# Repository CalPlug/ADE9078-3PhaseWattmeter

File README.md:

# ADE9078-3PhaseWattmeter
An Isolated design demo board using the ADE7953 3 phase AC wattmeter.  Design allows both WYE (STAR) and Delta (TRIANGLE) distributions to be measured along with Blondel and non-Blondel measurement schemes.  Project includes a demo ADE9078 Arduino firmware

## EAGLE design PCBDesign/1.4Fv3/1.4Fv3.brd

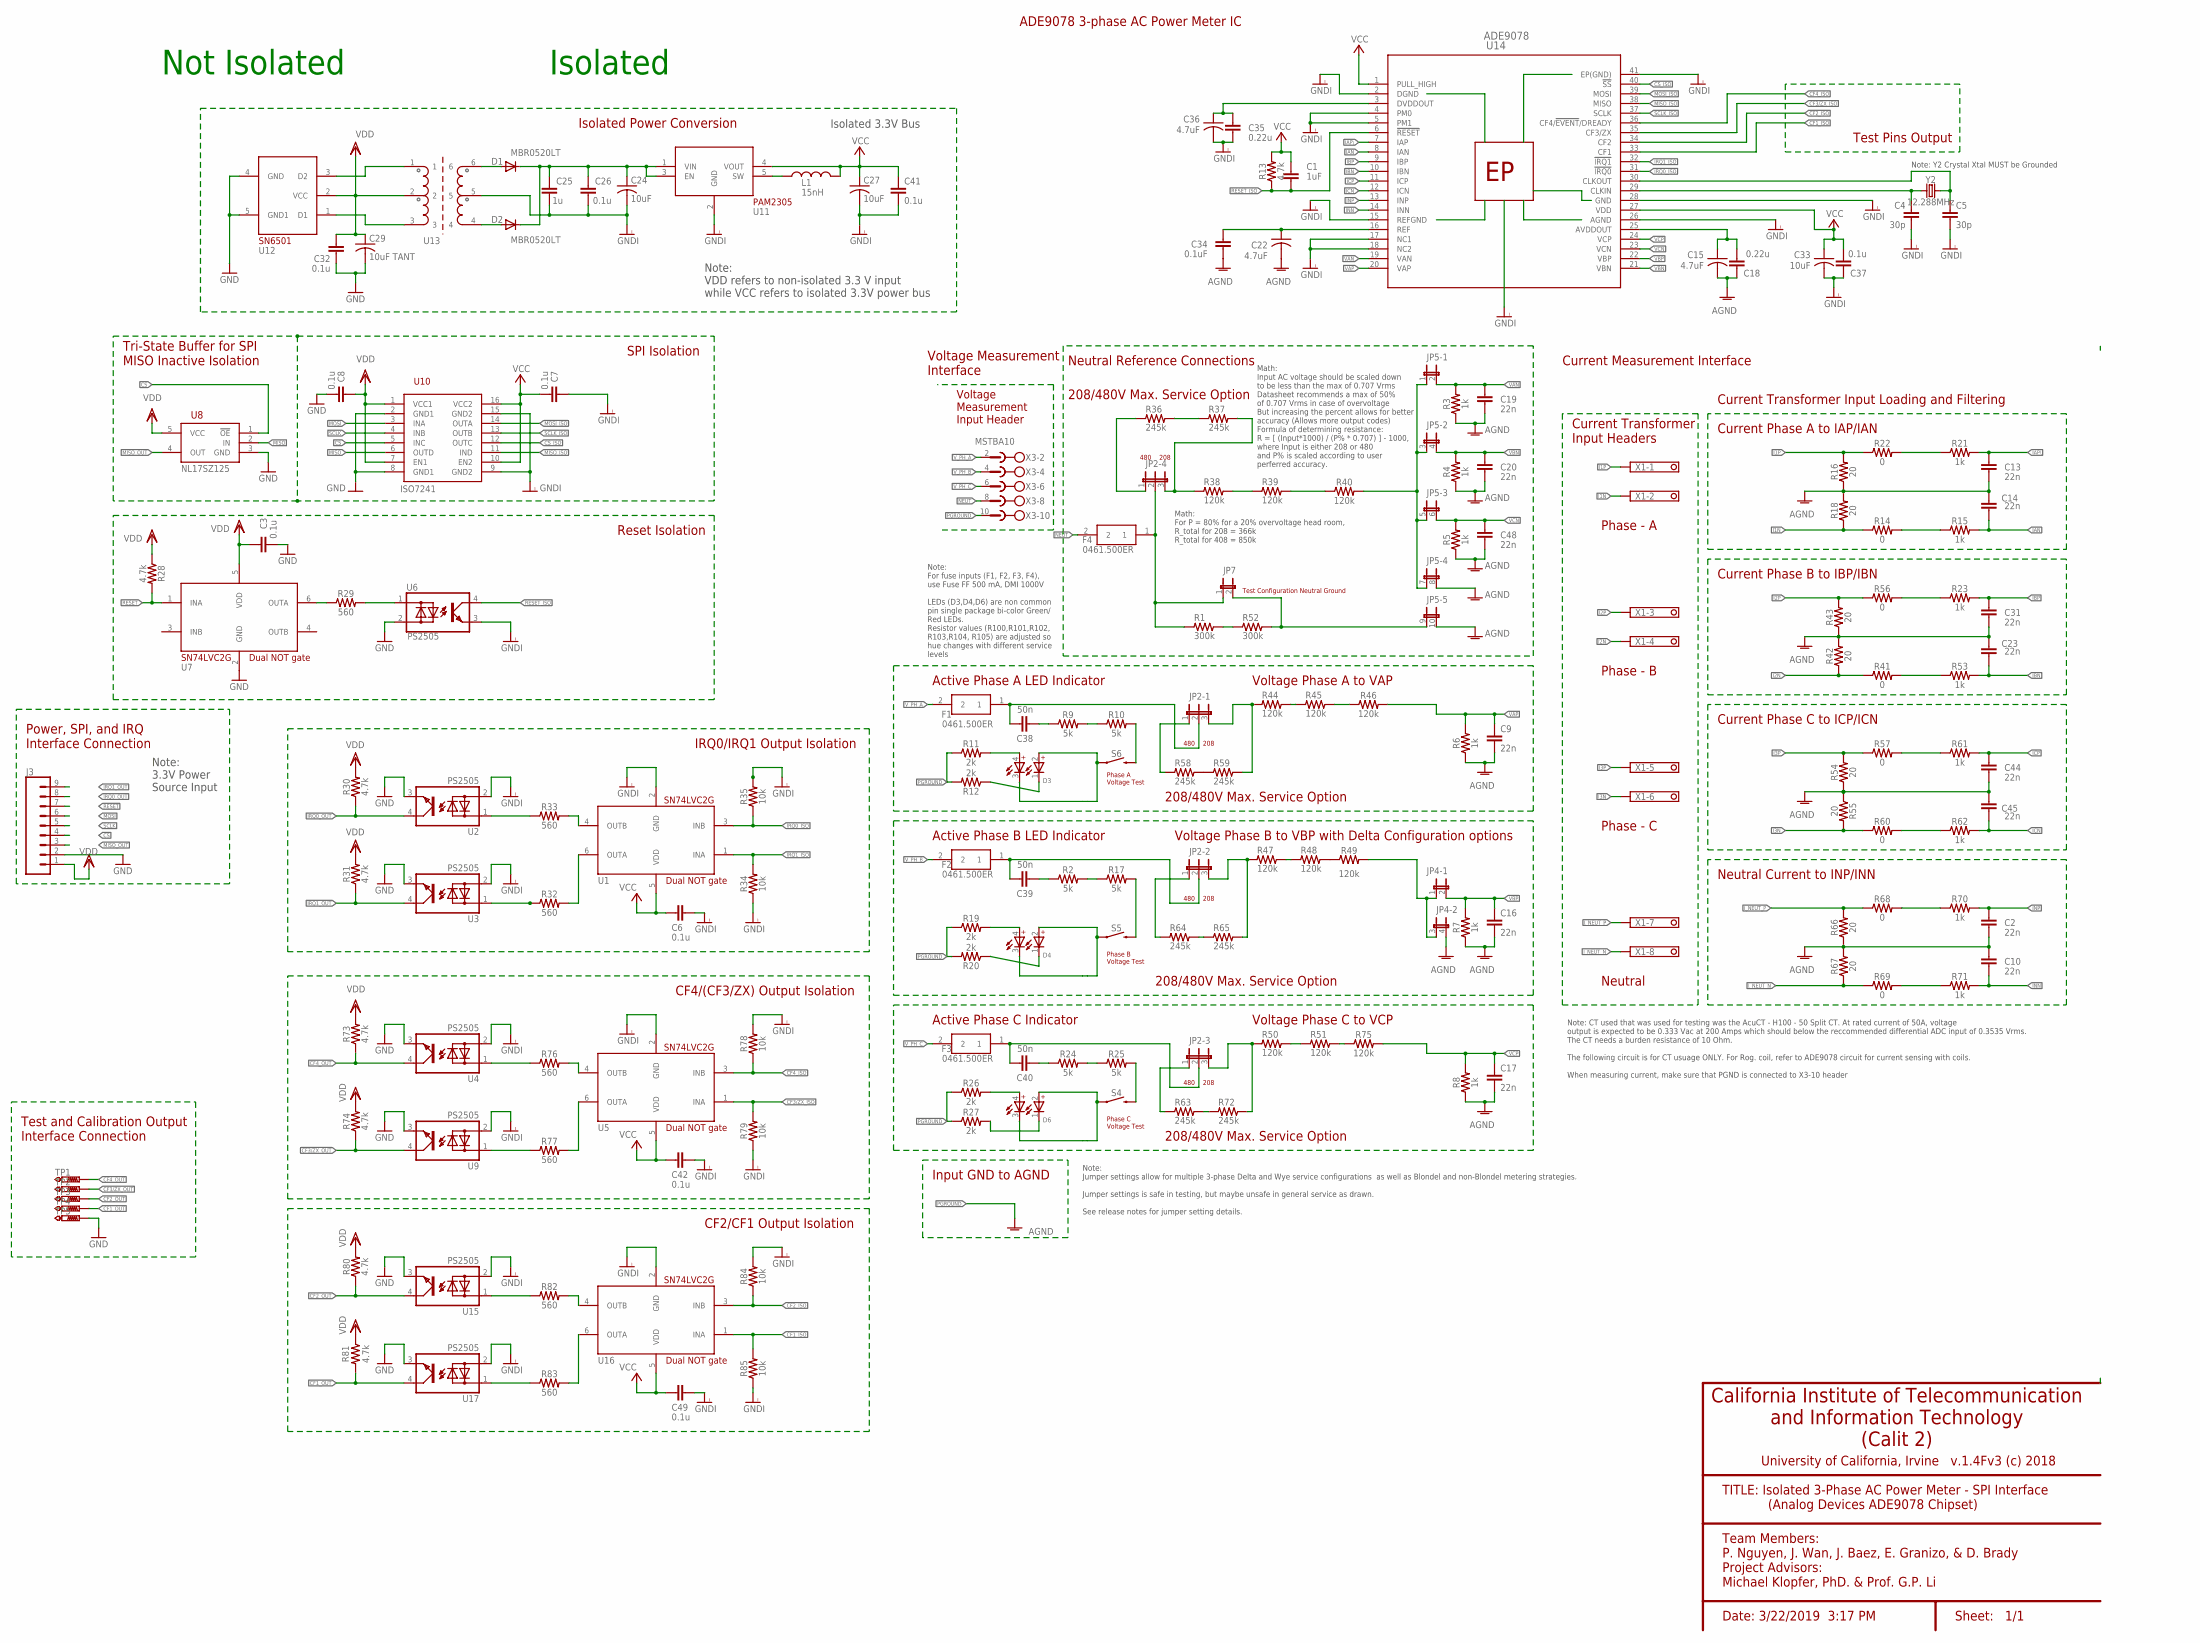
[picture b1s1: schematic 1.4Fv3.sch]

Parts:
C1: 1uF; 0603; MPN MC0805B104K500A5.08MM
C2, C9, C10, C13, C14, C16, C17, C19, C20, C23, C31, C44, C45, C48: 22n; 0402-CAP; MPN C0603C223K5RACTU
C3, C6, C7, C8, C26, C32, C37, C41, C42, C49: 0.1u; 0402-CAP; MPN C0603X5R1A104K030BC
C4, C5: 30p; 0402-CAP; MPN MC0402N180J500CT
C15, C22, C36: 4.7uF; C0603; MPN C1608X5R1A106K080AC
C18, C35: 0.22u; 0402-CAP; MPN MC0805F224Z500CT
C24, C27, C33: 10uF; C0603; MPN C1608X5R1A106K080AC
C25: 1u; 0402-CAP; MPN C0603X5R1A104K030BC
C29: 10uF TANT; C0603; MPN 195D106X96R3V2T
C34: 0.1uF; 0402-CAP; MPN C0603X5R1A104K030BC
C38, C39, C40: 50n; 0402-CAP; MPN C0603C223K5RACTU
D1, D2: MBR0520LT; SOD123; MPN MBR0520LT1G.
D3, D4, D6: WL-SBCW_0606_150066SV74000; WL-SBCW_0606
F1, F2, F3, F4: 0461.500ER; FUSC10131X312N
J3: CONN_09; 1X09; MPN 350547-1
JP2-1, JP2-2, JP2-3, JP2-4: JP2E; JP2
JP4: JP2QE; JP2Q; MPN 350547-1
JP5: JP5QE; JP5Q; MPN 350547-1
JP7: JP1E; JP1
L1: 15nH; 0402-RES
R1, R52: 300k; R2010
R2, R9, R10, R17, R24, R25: 5k; 0603
R3, R4, R5, R6, R7, R8, R15, R21, R23, R53, R61, R62, R70, R71: 1k; 0603
R11, R12, R19, R20, R26, R27: 2k; 0603
R13, R28, R30, R31, R73, R74, R80, R81: 4.7k; 0603
R14, R22, R41, R56, R57, R60, R68, R69: 0; 0603
R16, R18, R42, R43, R54, R55, R66, R67: 20; 0603
R29, R32, R33, R76, R77, R82, R83: 560; 0603
R34, R35, R78, R79, R84, R85: 10k; 0603
R36, R37, R58, R59, R63, R64, R65, R72: 245k; R2010
R38, R39, R44, R45, R47, R48, R50, R51: 120k; R2010
R40, R46, R49, R75: 120k; 0603
S4, S5, S6: MOMENTARY-SWITCH-SPST-SMD-4.5MM; TACTILE_SWITCH_SMD_4.5MM
TP1, TP2, TP3, TP4, TP5: PTR1B1,27; B1,27
U1, U5, U7, U16: SN74LVC; DCKT; MPN SN74LVC1G34DBVR
U2, U3, U4, U6, U9, U15, U17: PS2505; MPN PS2505-4-A
U8: NL17SZ125; MPN SN74LVC1G125DRLR
U10: ISO7241; 16-SOIC; MPN ISO7241CQDWRQ1
U11: PAM2305; TSOT25
U12: SN6501; SOT-23-5; MPN SN6501DBVT
U13: TRANSFO_3.3
U14: ADE9078; CP_40_7; MPN ADE9078ACPZ
X1: 1751303
X3: MSTBA10
Y2: 12.288MHz; CRYSTAL-SMD-5X3.2-4PAD

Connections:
AGND: C2.1, C9.2, C10.2, C13.1, C14.2, C15.2, C16.2, C17.2, C18.1, C19.2, C20.2, C22.2, C23.2, C31.1, C34.1, C44.1, C45.2, C48.2, JP4.4 (2), JP5.8 (2), JP5.10 (2), R3.1, R4.1, R5.1, R6.1, R7.1, R8.1, R16.1, R18.2, R42.2, R43.1, R54.1, R55.1, R66.1, R67.2
AVDDOUT: C15.1, C18.2, U14.25 (AVDDOUT)
CF1_ISO: R85.2, U14.33 (CF1), U16.1 (INA)
CF1_OUT: R81.2, TP4.TP, U17.4 (COLLERTOR)
CF2_ISO: R84.1, U14.34 (CF2), U16.3 (INB)
CF2_OUT: R80.1, TP3.TP, U15.4 (COLLERTOR)
CF3/ZX_ISO: R79.2, U5.1 (INA), U14.35 (CF3/ZX)
CF3/ZX_OUT: R74.1, TP2.TP, U9.4 (COLLERTOR)
CF4_ISO: R78.1, U5.3 (INB), U14.36 (CF4/!EVENT!/DREADY)
CF4_OUT: R73.1, TP1.TP, U4.4 (COLLERTOR)
CS: J3.4, U8.1 (!OE), U10.5 (INC)
CS_ISO: U10.12 (OUTC), U14.40 (!SS)
DVDDOUT: C35.2, C36.1, U14.3 (DVDDOUT)
GND: C3.2, C8.2, C29.2, C32.1, J3.2, TP5.TP, U2.3 (EMITTER), U3.3 (EMITTER), U4.3 (EMITTER), U6.2 (CATHODE), U7.2 (GND), U8.3 (GND), U9.3 (EMITTER), U10.2 (GND1), U10.8 (GND1), U12.4 (GND), U12.5 (GND1), U15.3 (EMITTER), U17.3 (EMITTER)
GNDI: C4.1, C5.2, C6.1, C7.1, C24.2, C25.1, C26.1, C27.2, C33.2, C35.1, C36.2, C37.1, C41.2, C42.1, C49.1, R34.1, R35.2, R78.2, R79.1, R84.2, R85.1, U1.2 (GND), U2.2 (CATHODE), U3.2 (CATHODE), U4.2 (CATHODE), U5.2 (GND), U6.3 (EMITTER), U9.2 (CATHODE), U10.9 (GND2), U10.15 (GND2), U11.2 (GND), U13.5, U14.2 (DGND), U14.4 (PM0), U14.5 (PM1), U14.15 (REFGND), U14.17 (NC1), U14.18 (NC2), U14.26 (AGND), U14.28 (GND), U14.41 (EP(GND)), U15.2 (CATHODE), U16.2 (GND), U17.2 (CATHODE)
I1N: R14.1, R18.1, X1.2
I1P: R16.2, R22.1, X1.1
I2N: R41.1, R42.1, X1.4
I2P: R43.2, R56.1, X1.3
I3N: R55.2, R60.1, X1.6
I3P: R54.2, R57.1, X1.5
IAN: C14.1, R15.2, U14.8 (IAN)
IAP\: C13.2, R21.2, U14.7 (IAP)
IBN: C23.1, R53.2, U14.10 (IBN)
IBP: C31.2, R23.2, U14.9 (IBP)
ICN: C45.1, R62.2, U14.12 (ICN)
ICP: C44.2, R61.2, U14.11 (ICP)
INN: C10.1, R71.2, U14.14 (INN)
INP: C2.2, R70.2, U14.13 (INP)
IRQ0_ISO: R35.1, U1.3 (INB), U14.31 (!IRQ0)
IRQ0_OUT: J3.8, R30.1, U2.4 (COLLERTOR)
IRQ1_ISO: R34.2, U1.1 (INA), U14.32 (!IRQ1)
IRQ1_OUT: J3.9, R31.1, U3.4 (COLLERTOR)
I_NEUT_N: R67.1, R69.1, X1.8
I_NEUT_P: R66.2, R68.1, X1.7
MISO: U8.2 (IN), U10.6 (OUTD)
MISO_ISO: U10.11 (IND), U14.38 (MISO)
MISO_OUT: J3.3, U8.4 (OUT)
MOSI: J3.6, U10.3 (INA)
MOSI_ISO: U10.14 (OUTA), U14.39 (MOSI)
unnamed: C5.1, U14.30 (CLKOUT), Y2.3 (2)
unnamed: R21.1, R22.2
unnamed: R14.2, R15.1
unnamed: L1.1, U11.5 (SW)
unnamed: R57.2, R61.1
unnamed: R60.2, R62.1
unnamed: C38.2, R9.1
unnamed: R32.2, U1.6 (OUTA)
unnamed: R32.1, U3.1 (ANODE)
unnamed: C4.2, U14.29 (CLKIN), Y2.1
unnamed: R25.2, S4.1 (2), S4.4 (2)
unnamed: D1.A, U13.6
unnamed: C24.1, C25.2, C26.2, D1.C, D2.C, U11.1 (VIN), U11.3 (EN)
unnamed: D2.A, U13.4
unnamed: U12.3 (D2), U13.1
unnamed: U12.1 (D1), U13.3
unnamed: R23.1, R56.2
unnamed: R29.2, U6.1 (ANODE)
unnamed: R29.1, U7.6 (OUTA)
unnamed: R41.2, R53.1
unnamed: R9.2, R10.1
unnamed: R33.2, U1.4 (OUTB)
unnamed: R76.2, U5.4 (OUTB)
unnamed: R1.2, R52.1
unnamed: R64.2, R65.1
unnamed: R33.1, U2.1 (ANODE)
unnamed: JP2-1.1, R58.1
unnamed: R58.2, R59.1
unnamed: R10.2, S6.1 (2), S6.4 (2)
unnamed: JP2-1.3, R44.1, R59.2
unnamed: JP2-2.1, R64.1
unnamed: JP2-2.3, R47.1, R65.2
unnamed: R63.2, R72.1
unnamed: R68.2, R70.1
unnamed: JP2-4.3, R37.2, R38.1
unnamed: JP2-4.1, R36.1
unnamed: R36.2, R37.1
unnamed: JP5.9 (1), JP7.2, R52.2
unnamed: R69.2, R71.1
unnamed: C39.2, R2.1
unnamed: R2.2, R17.1
unnamed: R17.2, S5.1 (2), S5.4 (2)
unnamed: D3.1 (C2), R12.1
unnamed: D6.2 (A2), D6.3 (C1), S4.2 (1), S4.3 (1)
unnamed: C40.2, R24.1
unnamed: R24.2, R25.1
unnamed: D3.4 (A1), R11.2
unnamed: D4.2 (A2), D4.3 (C1), S5.2 (1), S5.3 (1)
unnamed: R76.1, U4.1 (ANODE)
unnamed: R77.1, U9.1 (ANODE)
unnamed: R77.2, U5.6 (OUTA)
unnamed: JP5.1, JP5.3 (1), JP5.5 (1), JP5.7 (1), R40.2
unnamed: R82.1, U15.1 (ANODE)
unnamed: R83.1, U17.1 (ANODE)
unnamed: R83.2, U16.6 (OUTA)
unnamed: D3.2 (A2), D3.3 (C1), S6.2 (1), S6.3 (1)
unnamed: D4.4 (A1), R19.2
unnamed: R45.2, R46.1
unnamed: C40.1, F3.1, JP2-3.2
unnamed: F4.1, JP2-4.2, JP7.1, R1.1
unnamed: C38.1, F1.1, JP2-1.2
unnamed: R48.2, R49.1
unnamed: JP2-3.3, R50.1, R72.2
unnamed: JP4.1, JP4.3 (1), R49.2
unnamed: C39.1, F2.1, JP2-2.2
unnamed: JP2-3.1, R63.1
unnamed: R50.2, R51.1
unnamed: R51.2, R75.1
unnamed: R82.2, U16.4 (OUTB)
unnamed: R44.2, R45.1
unnamed: R47.2, R48.1
unnamed: R38.2, R39.1
unnamed: R39.2, R40.1
unnamed: D4.1 (C2), R20.1
unnamed: D6.1 (C2), R27.2
unnamed: D6.4 (A1), R26.2
NEUT: F4.2, X3.8
PGROUND: R11.1, R12.2, R19.1, R20.2, R26.1, R27.1, X3.10
REF: C22.1, C34.2, U14.16 (REF)
RESET: J3.7, R28.2, U7.1 (INA)
RESET_ISO: C1.2, R13.1, U6.4 (COLLERTOR), U14.6 (!RESET)
SCLK: J3.5, U10.4 (INB)
SCLK_ISO: U10.13 (OUTB), U14.37 (SCLK)
VAN: C19.1, JP5.2, R3.2, U14.19 (VAN)
VAP: C9.1, R6.2, R46.2, U14.20 (VAP)
VBN: C20.1, JP5.4 (2), R4.2, U14.21 (VBN)
VBP: C16.1, JP4.2, R7.2, U14.22 (VBP)
VCC: C1.1, C6.2, C7.2, C27.1, C33.1, C37.2, C41.1, C42.2, C49.2, L1.2, R13.2, U1.5 (VDD), U5.5 (VDD), U10.10 (EN2), U10.16 (VCC2), U11.4 (VOUT), U14.1 (PULL_HIGH), U14.27 (VDD), U16.5 (VDD)
VCN: C48.1, JP5.6 (2), R5.2, U14.23 (VCN)
VCP: C17.1, R8.2, R75.2, U14.24 (VCP)
VDD: C3.1, C8.1, C29.1, C32.2, J3.1, R28.1, R30.2, R31.2, R73.2, R74.2, R80.2, R81.1, U7.5 (VDD), U8.5 (VCC), U10.1 (VCC1), U10.7 (EN1), U12.2 (VCC), U13.2
V_PH_A: F1.2, X3.2
V_PH_B: F2.2, X3.4
V_PH_C: F3.2, X3.6

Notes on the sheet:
Not Isolated
Isolated
Isolated Power Conversion
Note: VDD refers to non-isolated 3.3 V input while VCC refers to isolated 3.3V power bus
Isolated 3.3V Bus
ISO7241
SPI Isolation
Tri-State Buffer for SPI MISO Inactive Isolation
Dual NOT gate
Reset Isolation
Power, SPI, and IRQ Interface Connection
Note: 3.3V Power Source Input
IRQ0/IRQ1 Output Isolation
CF4/(CF3/ZX) Output Isolation
Test and Calibration Output Interface Connection
CF2/CF1 Output Isolation
ADE9078 3-phase AC Power Meter IC
Current Measurement Interface
Test Pins Output
Voltage Measurement Interface
Voltage Measurement Input Header
Voltage Phase A to VAP
Voltage Phase B to VBP with Delta Configuration options
Voltage Phase C to VCP
Input GND to AGND
Neutral Reference Connections
Current Transformer Input Headers
Current Phase A to IAP/IAN
Current Phase B to IBP/IBN
Current Phase C to ICP/ICN
Neutral Current to INP/INN
Active Phase A LED Indicator
Active Phase B LED Indicator
Active Phase C Indicator
Current Transformer Input Loading and Filtering
Phase - A
Phase - B
Phase - C
Neutral
Date: 3/22/2019 3:17 PM

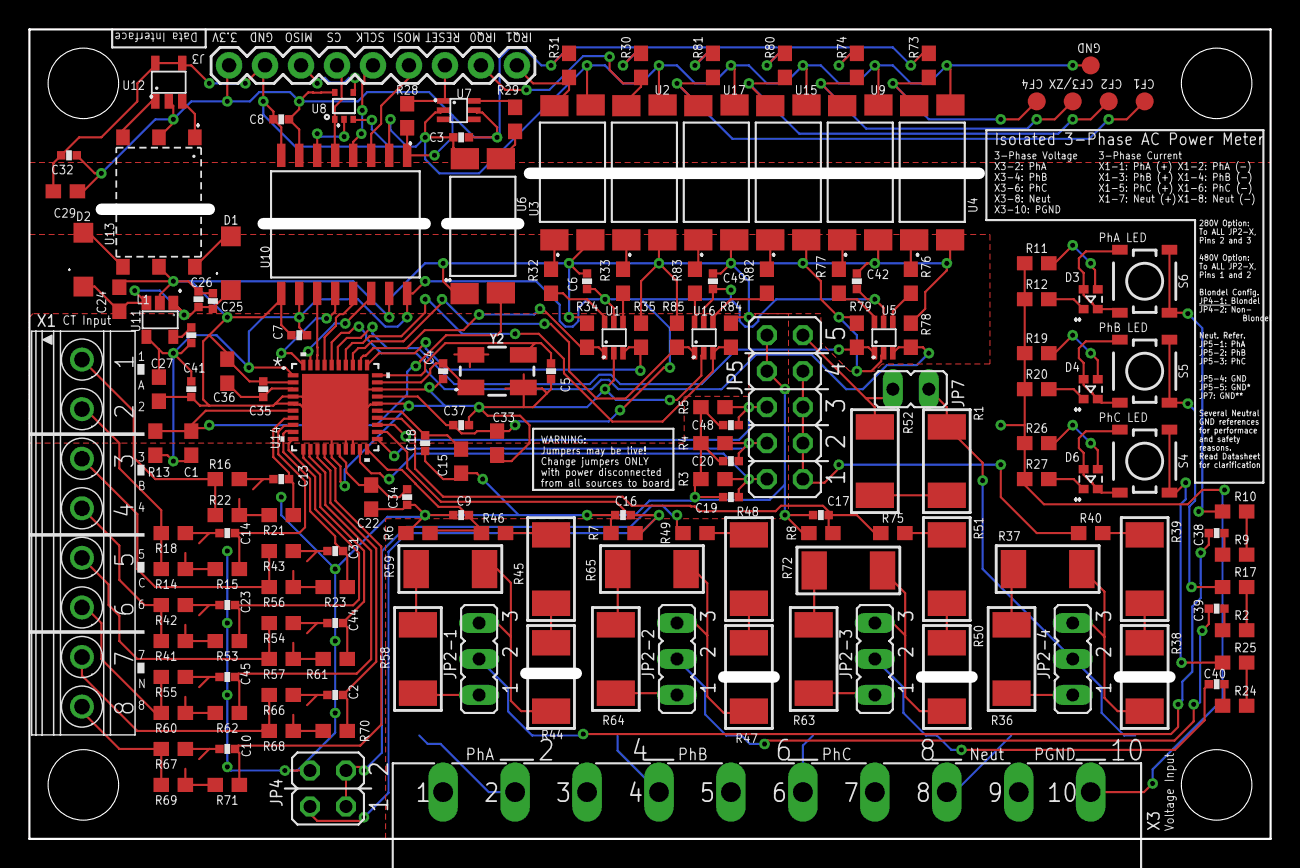
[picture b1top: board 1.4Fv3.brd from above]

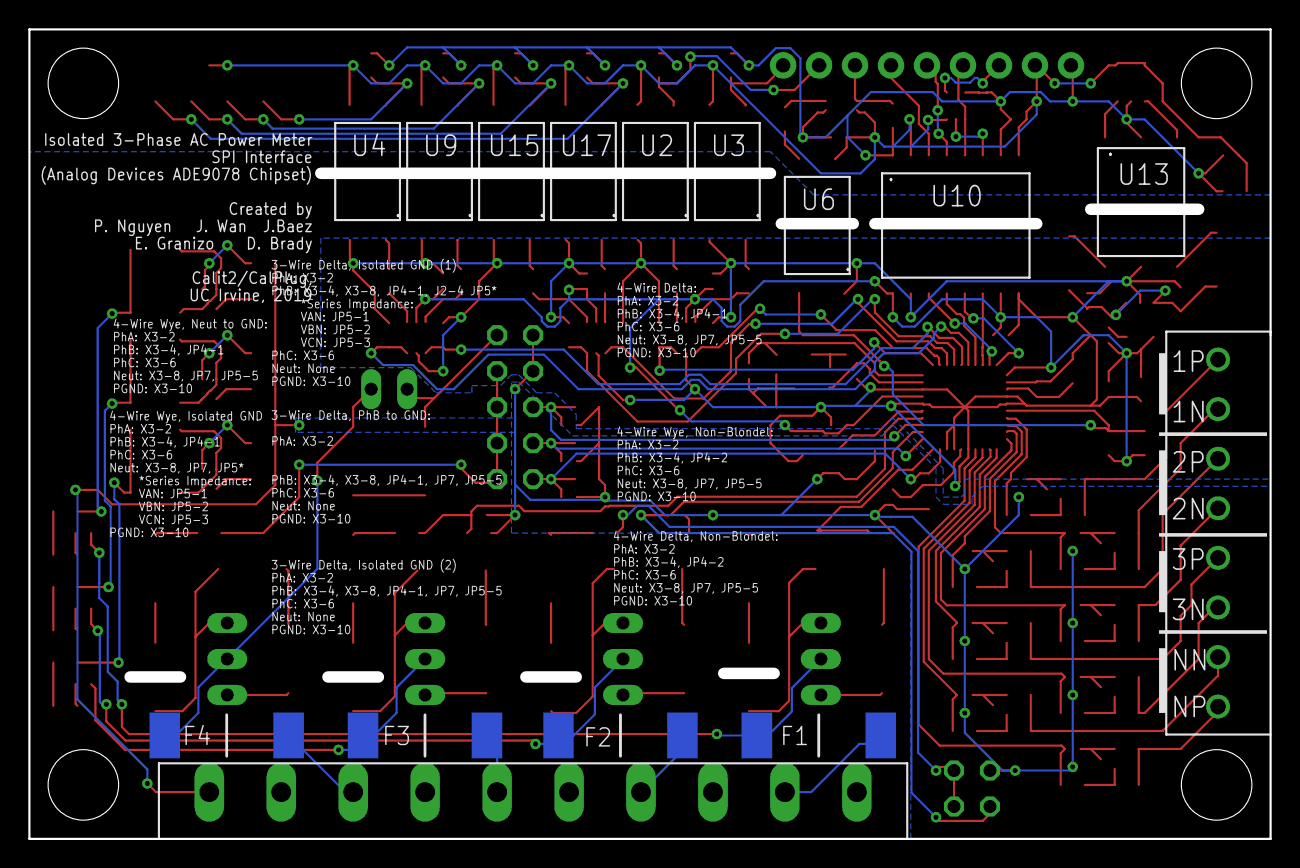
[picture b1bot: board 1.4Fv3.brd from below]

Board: 2 copper layers, 87.0 x 56.5 mm, 172 parts (4 on the bottom side), 134 nets.

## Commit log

2018-12-03 Initial Schematic
2018-12-03 Update Structure
2018-12-03 Version Update
2018-12-03 Update ESP32 Lib
2018-12-04 began adding register #define statements. incomplete. david/jacky/jeff
2018-12-04 Update Info
2018-12-05 finished adding defines. needs comments from p87 onwards
2018-12-05 Jwan- added comments to registers
2018-12-06 JWan--added additional register defines
2018-12-06 Jwan -- fixed a typo
2018-12-06 began removing duplicates and placing comments correctly. incomplete
2018-12-06 removed duplicate comments. registers at the end are dupes, and are the ones left that need comments
2018-12-06 finished two pages and deleted some of the repeats. Will finish tomorrow morning.
2018-12-06 defines and comments complete
2018-12-06 fixed #defines to have name first, register second
2018-12-06 cleaned comments. still needs reset/write
2018-12-06 begain adding reset/access comments
2018-12-06 Jwan--added reset/access
2018-12-07 added functions for a/b/c. getActiveEnergy, getReactiveEnergy, getApparentEnergy does not have funcs for all 3. needs comments for reset address and permissions on bits from end of datasheet
2018-12-07 Jwan-added reset and access
2018-12-07 added reset and access
2018-12-08 all commenting complete
2018-12-13 updated readme. version 0.1
2018-12-15 changed energy functions. just returns ACCMODE. might need to change to read certain bits. 0.2
2019-01-23 removed 8 bit/24 bit functions. also removed 7953 setup, as it is not required for 9078
2019-01-24 overhauled write functions. removed 8 bit and 24 bit functions
2019-01-24 deleted commented code that wont be used
2019-01-24 initial overhaul of reads/writes complete. all references to functionBitVal removed. registers need checking
2019-01-25 changed read/writes to correctly begin/end transactions
2019-01-29 first try at configuration
2019-01-31 updated header. updated demo. cleaned cpp
2019-01-31 removed some unnecessary comments. took out unused constants
2019-02-08 renamed header file
2019-02-08 handled compiler errors and warnings
2019-02-09 changed include to acount for file rename
2019-02-09 changed int to long to address overflow warning
2019-02-12 added phnoload to test file
2019-02-12 added version to demo
2019-02-14 Add Images of PCB
2019-02-14 Update Images
2019-02-14 Update Folder Structure
2019-02-16 added parameters to demo. implemented quick start in initialization
2019-02-23 split registers into separate file. 0'd out other config regs
2019-02-23 ade class now stores initialization data. also made destructor for the pointer to data
2019-02-23 made default settings in ade class to avoid retyping same thing. began rewriting debug lines
2019-02-23 added debug lines to spi reads/writes and initialize
2019-02-25 fixed debug lines
2019-02-27 renamed spi interface functions to be shorter. changed types to double and uint32_t
2019-02-27 added function to read channel A's watt hours
2019-02-28 Update Template Structure
2019-02-28 Update reporting structure
2019-02-28 Byte read in
2019-02-28 Update SPI transfer approach
2019-02-28 Update Bitval Lookup
2019-02-28 Update functionBitVal function input types
2019-02-28 Update Function Calls
2019-02-28 Update SPI settings for ESP32
2019-02-28 Update ESP32 Capability structure
2019-02-28 Update ESP32 SPI
2019-02-28 Update Variable Scopes
2019-02-28 Tested on ESP32 and Arduino for compile
2019-02-28 CRC Update
2019-02-28 Update CRC Example Code
2019-02-28 Update SPI redefinition issue
2019-02-28 Update SPI deff
2019-02-28 changed reads to correct command header
2019-02-28 fixed reads
2019-02-28 Update wiring mode selection
2019-02-28 Update Structure for wiring mode selection
2019-02-28 Update 9078 rebranding and debug output
2019-02-28 Update Calibration function
2019-02-28 Update with Signed Typecasting Approach
2019-02-28 Update Typecasting
2019-02-28 added file for calibrations
2019-03-01 Jacky: Raw Code Pushed to Repo
2019-03-03 added LastReads struct and substructs. Added read functions to set these values
2019-03-03 Update CRC functions
2019-03-03 Update ESP32 compatability for CRC
2019-03-03 Update notes in the code
2019-03-03 Basic EEPROM handler functions included
2019-03-03 Update EEPROM Approach
2019-03-04 fixed indentation in .h. added most functions in 9000. typecasted before assigning
2019-03-05 Update Template Calibration Firmware
2019-03-05 Update EEPROM Inclusion
2019-03-06 added code and demo for waveform sampling. not tested.
2019-03-06 turns out staying awake cause you're thinking about koding helps you find bugs before you even test
2019-03-06 peter's work: updated registers in calibration demo
2019-03-06 put jackys crc algorithm in. not compiling since it only takes 1 algorithm
2019-03-07 broken. assignment not working
2019-03-08 maybe fixed seg fault bug. allocated space for fullResample
2019-03-08 changed byte* to unsigned char* -Jacky
2019-03-12 Added new algorithm from source found - Jacky
2019-03-12 added source for previous algorithm- J
2019-03-12 implement CRC-XMODEM (MSB), comment for 0xffff implementation-Jacky
2019-03-12 attempted debugging resampled demo. not able to assign still
2019-03-12 Most recent (March 2019) Design update
2019-03-13 fft demo compiling. not tested
2019-03-13 calibration files edits
2019-03-13 calibrated voltage gain/offset. Unsure about current
2019-03-13 took out power variables
2019-03-13 jumper config
2019-03-15 added prints for debugging. fft demo not working. waveform sample demo running, but reading trash data. move variable declarations to functions to avoid crash on assign (sketch mem is read only)
2019-03-15 changed demo.ino to just print A and B rms to serial
2019-03-15 added jeff's processing code
2019-03-16 Update Closeout Notes
2019-03-16 Create ResampledFFTTemplate.ino
    Sample Layout for FFT based analysis
2019-03-17 resources for future fpga design team - Jacky
2019-03-17 revert back, see Crc_work_archive for moved code-J
2019-03-17 crc work for archival-J
2019-03-22 Schematic update
2019-03-22 Updated for the schematic changes
2019-03-26 added new devreadme
2019-04-05 Update Folder Structure for Archiving
2019-04-10 Updated Schematic new version 1.4Fv4
    Updated notes on second pole filter
2019-04-10 Push up schematic with changes
2019-04-10 Changed resistor values 0->100
2019-04-10 Added pdf file of schematic
2019-04-10 Reorganized documents
2019-04-11 Adjusted notes
2019-04-12 Pushed the updated version of the BOM
2019-04-17 Cleanup firmware notes
2019-04-17 Update with David's comments
2019-04-18 Updated BOM, changed schematic, and uploaded PDF of latest version under documents
2019-04-19 Update Locations
2019-04-19 Moved files around and replaced old PDF
2019-04-23 Updated new BOM format
2019-04-23 PDF of PCB
2019-04-28 processing 3 graphing demo
    only implemented Av and Bv, i want to test on the actual unit before
    adding the rest.
    the other V,I,and P should be easy to implement, just some copy and
    pasting.
2019-04-28 added Cv
2019-04-28 finished processing demo
2019-04-28 update read me
2019-04-28 bug fix
2019-04-29 processing demo updates
    -error threshold values for each individual value (Av, Bv, Bi, I
    neutral, etc.
    -added in neutral I, V, P
2019-05-05 some wfb functions
    WFB: mode 0 mostly impleneted, working on mode 1
    still need to create interrupt functions to give data to user.
2019-05-06 new wfb demo
    updated wfb demo to be more inline with functions i created.
    still have to add the wfb functions to the ADE9078.cpp main library file
2019-05-06 cleaned up code
2019-05-07 WFB update
    -added new WFB configuration function
    -updated resampleWFB
2019-05-08 FFT demo 2
2019-05-08 bug fixes for resampledFFT2 demo
    i promise i'll start verifying before pushing next time lol
2019-05-14 wfb burst read
2019-05-14 updates to fft2
    i removed a bunch of print statements in the library
2019-05-15 back to square 2
2019-05-15 resampled wfb & fft tests
2019-05-15 instructions for processing demo
2019-05-16 figuring out fft & fft examples
2019-05-16 finilization of main cpp file
    also processing demo
2019-05-28 cleaned up codes
2019-05-29 Updated CRC
2019-06-03 fixed wfb
    had current and voltage reading in the wrong places
2019-06-04 blondel total current graphing option
2019-06-07 Helper program for calibration
2019-06-07 Linear FABLS
2019-06-07 FABLS and ardprintf
2019-06-07 FABLS
2019-06-08 cleaning
2019-06-12 readme
2019-06-12 DEV readme update
2019-06-13 renamed file to fix issue
2019-06-14 PDF of final PCB board design
    Uploaded final PCB board design (PDF)
2019-06-14 PDF of schematic

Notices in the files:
PCBDesign/1.4Fv3/1.4Fv3.sch:
University of California, Irvine v.1.4Fv3 (c) 2018
parts and their libraries:
SparkFun-Connectors: Licensing: Creative Commons ShareAlike 4.0 International - https://creativecommons.org/licenses/by-sa/4.0
Wurth_Elektronik_Optoelectronics_rev18a: Copyright: Würth Elektronik
rc-master-smd: Copyright (C) 2007, Bob Starr
